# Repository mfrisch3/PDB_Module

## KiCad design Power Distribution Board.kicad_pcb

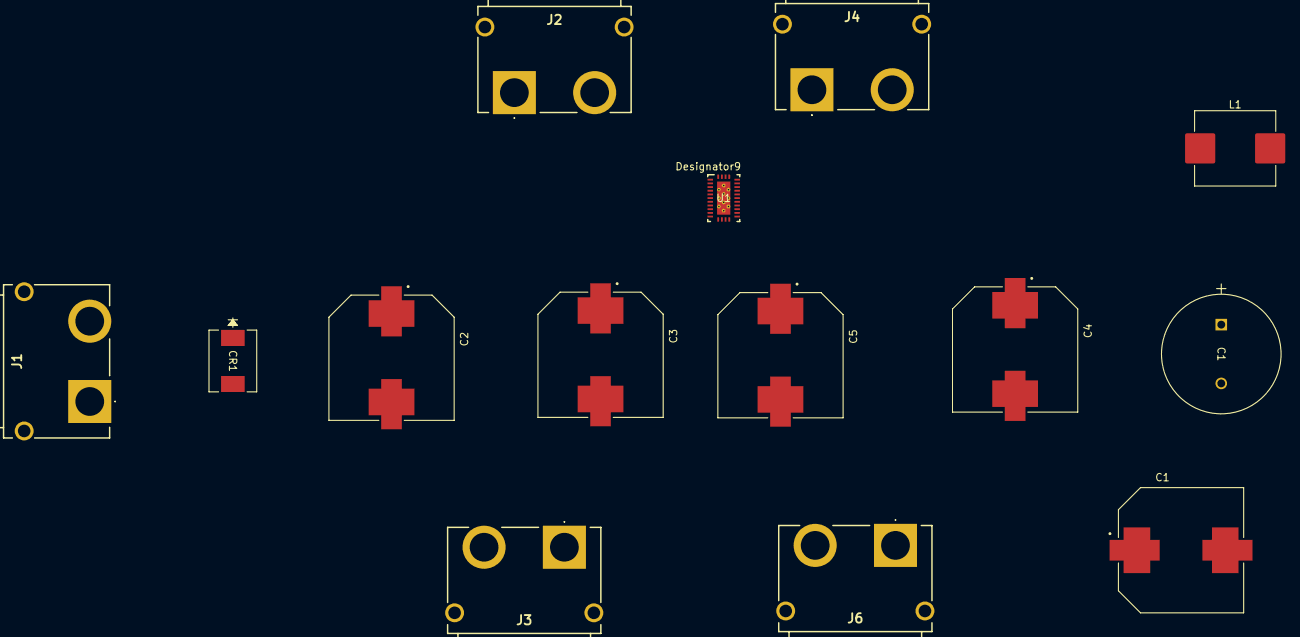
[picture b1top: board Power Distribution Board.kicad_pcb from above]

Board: 2 copper layers, 14 parts (0 on the bottom side), 5 nets, no tracks yet.

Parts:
C1: 1000uF; CAP_16 X 25_PAN
C1#2, C2, C3, C4, C5: 470uF; CAP_EEVFK1J471V
CR1: 5.0SMDJ36A; 5.0SMDJSeries_LTF
J1, J2, J3, J4, J6: XT90PW-F; XT90PWF
L1: 10uH; L_APV_APH1030
U1: LM76003RNPR; RNP0030B

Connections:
0: U1.7 (NC), U1.13 (AGND), U1.14 (AGND), U1.15 (AGND), U1.17 (SYNC_MODE), U1.19 (NC), U1.23 (NC), U1.24 (PGND), U1.25 (PGND), U1.26 (PGND), U1.27 (NC), U1.28 (NC), U1.29 (NC), U1.30 (NC), U1.31 (PAD)
GND: C1#2.2, C2.2, C3.2, C4.2, C5.2, CR1.2, J1.1 (+), J2.3 (MH1), J3.3 (MH1), J4.3 (MH1)
unnamed: L1.1, U1.1 (SW), U1.2 (SW), U1.3 (SW), U1.4 (SW), U1.5 (SW)
unnamed: L1.2, U1.9 (BIAS)
unnamed: C1.1, C1#2.1, C2.1, C3.1, C4.1, C5.1, CR1.1, J1.2 (-), J2.4 (MH2), J3.4 (MH2), J4.4 (MH2), U1.18 (EN), U1.20 (PVIN), U1.21 (PVIN), U1.22 (PVIN)
